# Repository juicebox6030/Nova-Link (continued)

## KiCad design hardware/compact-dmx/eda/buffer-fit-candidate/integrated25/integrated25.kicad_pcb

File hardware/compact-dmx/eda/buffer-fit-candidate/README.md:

# Buffer fit candidate — isolated proposal, 2026-10-23

**Preferred engineering candidate: Eaton HV1625-2R7256-R, 25 F**, with a local PCB aperture and lowered horizontal cradle. Conditional aged runtime is **16.343 s**, versus **9.730 s** for the existing 15 F. This is useful margin over the owner's 10 s minimum and the approximately12 s engineering screen, not measured runtime or lifetime qualification. The case remains98×34×24. No baseline or other candidate was edited. Parent must choose/integrate after Sol's concurrent startup correction.

## Sources and bounded comparison

Three families only: Eaton HV, KYOCERA AVX SCC, CDA CXHP. Actual primary PDFs and extracted text are in `sources/`; exact URLs, document identifiers and SHA256 are in `sources.json`. Eaton's primary asset was recovered through the existing browser after CLI failures. AVX and CDA were retrieved directly. Manufacturer dimension pages were rendered and inspected, with no pixel-derived dimensions.

| Exact MPN | Maximum body Ø × L mm | Initial ESR used | Aged C / ESR screen | Runtime s | Disposition |
|---|---:|---:|---:|---:|---|
| HV1325-2R7156-R |13.5×28.4|30mΩ|9.45F /60mΩ|9.730|Existing, fails conditional10s |
| **HV1625-2R7256-R** |**16.5×28.4**|27mΩ|15.75F /54mΩ|**16.343**|Preferred with explicit cutout |
| SCCT30B186SRB |13.5×32|60mΩ DC5s|11.34F /120mΩ|10.764|Little margin; body consumes3.6mm more lead reserve |
| SCCT35B226SRB |13.5×37|58mΩ DC5s|13.86F /116mΩ|13.230|Body alone exceeds35mm longitudinal reserve; not selected |
| CXHP2R7206R-TW |13.5×26.5|60mΩ DC|11.2F /120mΩ|10.631|Fits old body envelope, insufficient useful margin |

Sources: Eaton Technical Data4376 effectiveJan2020 pp2–3; AVX TDS-SC-0001 Rev11 pp2–4; CDA2024 catalog pp4,10–11. For AVX use the slower DC5s resistance, not the attractive1kHz figure. AVX maxima include +1mm diameter/+2mm length; CDA includes +1mm diameter/+1.5mm length. These are nominal starting-value substitutions only; no supplier procurement/lifecycle approval was obtained.

## Reproducible energy/ESR screen

`screen.py` independently solves constant-power discharge. With output load1.11W and electronics efficiencyη, cell terminal power is P=1.11/η. At internal voltage V and ESR R, terminal voltage is `(V+sqrt(V²−4RP))/2`; current is P/Vterminal. Stop when **loaded** terminal voltage reaches1.705917V, so internal end voltage is floor+RP/floor. Integrate `dt=C*Vterminal/P*dV` from this end to2.448V. ESR loss is explicit, not deducted twice through an assumed combined efficiency.

Initial tolerance and aging remain separate:25×0.9×0.7=15.75F. Eaton's endurance/cycle limit permits200% initial maximum ESR;54mΩ is the screen. These test limits at stated conditions are **not a field-age or cold guarantee**. Simpson integration agrees with an independent100µs forward-time integration within0.001s;10k vs20k integration panels agree within1e−8s. Existing15F result reproduces9.729548s.

At cutoff the25F screen draws0.813A and dissipates35.7mW in ESR. Manufacturer20°C references list3.4A continuous for15°C rise in open air and20A one-second pulse; neither qualifies the enclosed fixture duty cycle. At70% efficiency and twice aged ESR (108mΩ), runtime13.018s; at70% and162mΩ,11.893s. These are sensitivity allocations, **not sourced cold multipliers**. Cold capacitance can fall as well: an additional0.7 capacitance factor would reduce the latter to8.325s. Eaton does not provide a guaranteed combined aged/cold bound here. AVX typical temperature plots and CDA's temperature-change limits likewise do not establish a simultaneous lifetime/temperature guarantee for the preferred cell.

Retain2.6V nominal charging and all existing cutoff/rearm thresholds; no resistor changes proposed. Raising voltage is not the selected fix: even ignoring ESR, the aged15F needs2.5365V usable starting voltage for12s, above the existing2.448V reserved start. Removing the100mV historical reserve would require validating regulation/arming/load behavior; it is not free energy margin. At2.7V maximum rating there is no justification to consume the existing tolerance/overshoot allowance.

## Exact packaging proposal

Editable `geometry.py`, `buffer25-proposal.FCStd` and analytic `buffer25-proposal.step` are a **separate** geometry proposal. They copy frozen GCT shapes read-only; no baseline writer is imported. `fit-section.svg/pdf` are dimensioned equal-scale views.

- Existing board mainx4..94,y23..51,z10..11 and USB tongue remain. **New aperture** x26.5..55.9,y25.5..35.8,29.4×10.3 through the board; square corners are conceptual and require routed internal radius/strength/DFM design. It stays right of isolation boundaryx26 and below the RF allocationx59.
- Cell maximum body moves fromx26..54.4,cy30.25,cz18.75 to **x27..55.4,cy30.65,cz18.1**. Maximum body bottom9.85/top26.35 and y22.4..38.9. It crosses the PCB plane, so an unchanged board is impossible. High-body projection extends outside the oldy23.5..37 reserve; this is explicitly a new3D reserve, not silent reuse of its area.
- Two proposed PA12 saddles x28..31 and50..53,y25.8..35.5,z7..12.5 are cut to radius8.60. They contact the case floor atz7 and clear the aperture. Nominal radial gap0.35 is for a **not yet modeled/specified compliant liner**. Cell-position0.15 plus saddle-process0.10 leaves0.10 rigid radial margin. Positive retention, adhesive/mounting method, vent relief, load/creep and compression must be designed/qualified; no retention solution is claimed from the saddle alone.
- Supplier leads change fromØ0.60 to **Ø0.80±0.02**, pitch **7.5±0.5** (previous5mm). Existing C23 lands atx27.5 are removed from this proposal's check and must be replaced, not reused. Proposed **lead-form reservation** x55.4..58.9,y26..35.3 with potential landing nearx58 and nominaly26.9/34.4, stays before RFx59. This is an allocation only: allowable bend radius/seal standoff, lead strain relief, hole/annulus/pitch accommodation and solder volume are unresolved. No exact formed-lead CAD or released footprint is fabricated.
- GCT support/stop/port, NOR, screw bosses and external98×34×24 remain untouched. No cable-fit, PCB-strength, EMC or RF-clearance qualification follows from this geometry.

Nominal wall/lid clearance0.40/0.65mm. Inflating the maximum cell by0.15mm radially and each end gives wall0.25/lid0.50; a further0.10mm inward case/lid process allowance leaves **0.15/0.40mm**. With aperture edges inset0.10 and PCB top11.10, the inflated cell has **0.231mm** actual BRep PCB clearance. These are allocated process limits requiring manufacturer agreement, not measured assembly capability.

The independent geometry screen finds16 valid closed solids,15 cell-to-other-solid comparisons, and173 component-courtyard extrusions with **zero intersections**, plus cradle checks. Four mounting footprints have empty courtyard caches; physical bosses/holes are instead in the frozen solids. Top heights use conservative2.23mm, except nearbyU24/U26 at source DBV maximum1.45mm andR15 at deliberately loose1.45mm (Vishay actual0402 maximum0.40mm); bottom heights1.45mm. The initial uniform2.23mm screening flagged these three, then source-height refinement cleared them. This is not supplier-exact assembled component CAD. The original37 positions, USB, NOR and power placements are not edited or re-routed. **No new KiCad DRC is claimed**: this is an aperture proposal, not a modified electrical board.

## Charge, voltage, protection and release gates

25mA remains: nominal empty-to2.6V takes**43.33min before CV tail**, versus26min. Using32.5F,2.652V and22.42mA gives**64.07min before tail**, conditional on the existing charger assumptions; no recharge-interval requirement is invented. Leakage45µA is nominal after72h at20°C, not a worst-case aged/cold bound. NormalUSB still requires5V advertisement≥1.5A; no changes to qualification or current limiting.

Preferred cell rating2.7V,−40..+65°C; extension to85°C requires linear derating to2.3V.2.6V nominal is not authorized across that entire extended range.3.0V surge is not a permissible charge target. Do not reverse or overvoltage. Stored energy grows to84.5J nominal at2.6V, up to118.46J at32.5F/2.7V.100A short-circuit reference is a safety number, not operating current or protection guarantee.

Existing absence of independent cell OVP/fuse remains a **hardware protection-policy gate**: a charger feedback fault can overcharge below input-current-trip level; a cell-side short bypasses upstream protection. Larger capacitance increases fault energy. This package does not quietly add or qualify protection. Before release: supplier lead/temperature/capacitance/ESR confirmation; cell OVP/short policy; charger low-voltage behavior and leakage; empty startup/hot reattach afterU40 correction; measured worst-activity runtime at temperature/age; cradle/retainer/vent/assembly tolerance; new C23 lands and routing/PCB cutout strength; full RF/mechanical qualification.

## Concurrency and reproduction

`inputs.json` records initial read hashes; `placement-boxes.json` separately records the exact actual-board hash used for173 volume screens. Sol changed `DESIGN.md`, `corner-proof.py`, `corner-proof.json` and the live board during this pass, as expected. `screen.json` reports those changes rather than overwriting input hashes. **This proposal is against the frozen extracted geometry and fixed user-specified electrical corner, not acceptance of the final Sol revision.** Parent must compare/re-extract after integration; no power-file mutation was made here.

From repo root:

```sh
python3 hardware/compact-dmx/eda/buffer-fit-candidate/screen.py
NOVA_BUFFER_FIT="$PWD/hardware/compact-dmx/eda/buffer-fit-candidate" QT_QPA_PLATFORM=offscreen /home/juicebox/.local/bin/freecadcmd hardware/compact-dmx/eda/buffer-fit-candidate/geometry.py
python3 hardware/compact-dmx/eda/buffer-fit-candidate/draw.py
```

`extract-placement.py` is the read-only KiCad extraction tool used once; it writes only here. Do not rerun it against a changed source and call that the same evidence. `freeze.py` refuses to overwrite its initial record. `receipt.json` holds artifact/source hashes and final checks. No hardware operation, firmware, installation, publication, baseline edits or product acceptance.

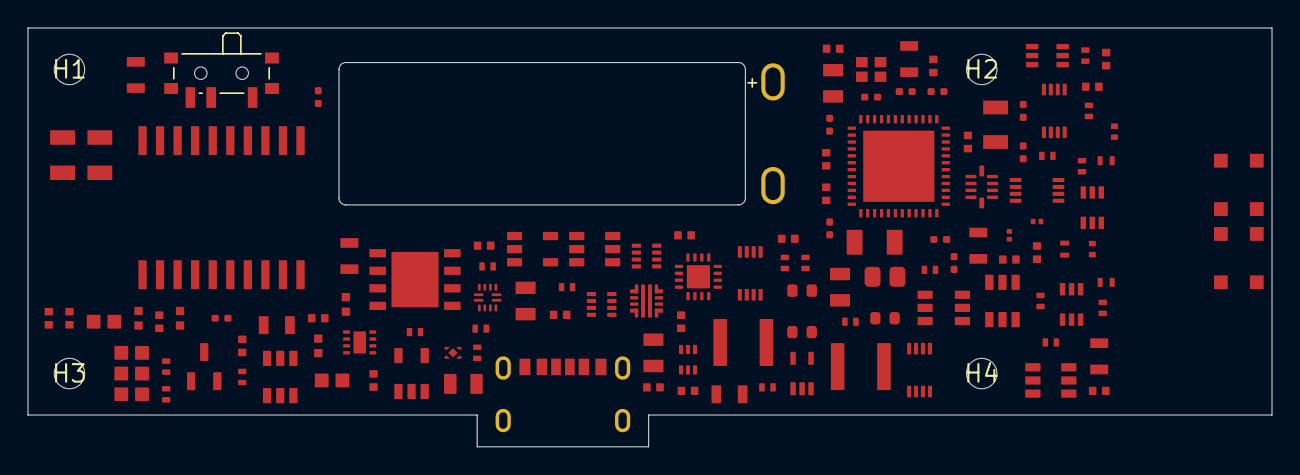
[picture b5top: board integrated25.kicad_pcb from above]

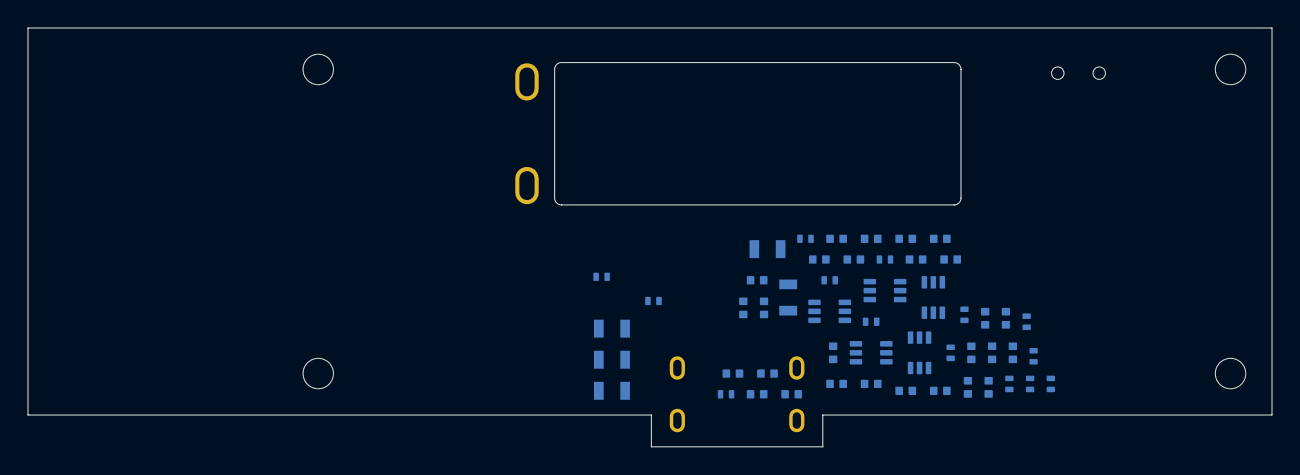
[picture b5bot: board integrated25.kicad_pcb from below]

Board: 2 copper layers, 90.0 x 30.3 mm, 178 parts (51 on the bottom side), 105 nets, no tracks yet.

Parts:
BASE_A101: 0900AD47A2450001E PROTOTYPE TUNING REQUIRED; Johanson_0900AD47_IsolatedLands
BASE_C1, BASE_C3: GRM155R71E104KE14D 100nF 25V X7R; TI_CAPC1005_Vector
BASE_C2, BASE_C4: GRM21BR71A106KE51L 10uF 10V X7R; Murata_GRM21_Reflow
BASE_C101, BASE_C102: GRM188R60J226MEA0D 22uF; TI_CAPC1608_Vector
BASE_C103: GRM155R61C105KA12D 1uF; TI_CAPC1005_Vector
BASE_C104, BASE_C105, BASE_C106, BASE_C107, BASE_C108, BASE_C109: GRM155R71E104KE14D 100nF; TI_CAPC1005_Vector
BASE_C110, BASE_C111: GRM1555C1H120JA01D 12pF; TI_CAPC1005_Vector
BASE_C112, BASE_C113: GRM0335C1H101GA01D 100pF; TI_CAPC0603_Vector
BASE_C115: GJM1555C1H1R0BB01D 1.0pF TUNE; Murata_GJM155_Manufacturer
BASE_C116: GJM1555C1H8R2DB01D 8.2pF TUNE; Murata_GJM155_Manufacturer
BASE_FL101: BLM18HE152SN1D; TI_BLM18_Vector
BASE_L101: MLZ2012N6R8LT000 6.8uH; TI_MLZ2012_Vector
BASE_L102: 0402HP-2N7XGRW 2.7nH TUNE; Coilcraft_0402HP_Manufacturer
BASE_L103: 0402HP-5N1XGRW 5.1nH TUNE; Coilcraft_0402HP_Manufacturer
BASE_L104: 0402HP-12NXGRW 12nH TUNE; Coilcraft_0402HP_Manufacturer
BASE_R1, BASE_R2, BASE_R3: CRCW040210K0FKED 10k 1%; Vishay_CRCW0402
BASE_R4: CRCW04021K00FKED 1k 1%; Vishay_CRCW0402
BASE_R_TERM1, BASE_R_TERM2: CRCW1206240RFKEA 240R 1% 0.25W; Vishay_CRCW1206
BASE_S_TERM: PCM12SMTR OFF=1-2 / ON=2-3; PCM12_PENDING_MANUFACTURER_LAND_RECHECK
BASE_TR101: 0900PC15A0036001E; TI_IPC1352_Vector
BASE_U1: CC1352R1F3RGZR; TI_RGZ0048A
BASE_U5: ISOW1412DFMR; TI_DFM0020A
BASE_Y101: FC-135 32.7680KA-AG0; Epson_FC135_Manufacturer
BASE_Y102: NX2016SA 48MHz EXS00A-CS05517; NDK_NX2016SA_Manufacturer
C1, C7, C15, C16, C17, C18, C21: GRM155R61C105KA12D 1uF 16V X5R; C0402
C2, C3, C22: GRM155R71H103KA88D 10nF 50V X7R; C0402
C4, C5, C24, C25, C26, C27, C28, C29, C30, C31, C32, C33, C34, C35, C36, C37, C38, C39, C40, C41, C42, C43, C44, C45: GRM155R71E104KE14D 100nF 25V X7R; C0402
C6, C8, C9, C10, C11, C12, C13, C14, C19, C20: GRM21BR71A106KE51L 10uF 10V X7R; C0805
C23: HV1625-2R7256-R 25F 2.7V; HV1625_formed_ENGINEERING
H1, H2, H3, H4: Mechanical NPTH 2.2
J1: USB4125-GF-A; USB_GCT
J4: Fabricated six-pad cJTAG/reset/ROM; VREF sense on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; Factory6
L1: XGL4020-222MEC 2.2uH 20%; L4020
L2: XFL4020-222MEC 2.2uH 20%; L4020
R1: TNPW1206150RBEEA 150ohm 0.1% 25ppm; R1206
R2: TNPW0805330RBEEA 330ohm 0.1% 25ppm; R0805
R3: TNPW040222K1BEED 22100ohm 0.1% 25ppm; R0402
R4, R6, R7, R8, R12, R13, R15, R21, R25, R27, R29, R31, R33, R35, R37, R38, R39, R40, R43, R44, R45, R46: TNPW040210K0BEED 10000ohm 0.1% 25ppm; R0402
R5: TNPW0805909KBEEA 909000ohm 0.1% 25ppm; R0805
R9: TNPW0805249KBEEA 249000ohm 0.1% 25ppm; R0805
R10: TNPW0805115KBEEA 115000ohm 0.1% 25ppm; R0805
R11: TNPW04023K32BEED 3320ohm 0.1% 25ppm; R0402
R14, R18: TNPW0402100RBEED 100ohm 0.1% 25ppm; R0402
R16, R17, R23, R41, R42, R47, R48, R56: TNPW0402100KBEED 100000ohm 0.1% 25ppm; R0402
R19: TNPW040211K9BEED 11900ohm 0.1% 25ppm; R0402
R20: TNPW040222K5BEED 22500ohm 0.1% 25ppm; R0402
R22: TNPW0805562KBEEA 562000ohm 0.1% 25ppm; R0805
R24: TNPW040232K4BEED 32400ohm 0.1% 25ppm; R0402
R26: TNPW040252K3BEED 52300ohm 0.1% 25ppm; R0402
R28, R32: TNPW040289K8BEED 89800ohm 0.1% 25ppm; R0402
R30, R34: TNPW040280K6BEED 80600ohm 0.1% 25ppm; R0402
R36: TNPW04024K70BEED 4700ohm 0.1% 25ppm; R0402
R49: TNPW040233K0BEED 33000ohm 0.1% 25ppm; R0402
R50, R51, R52, R53, R54, R55: TNPW040247K0BEED 47000ohm 0.1% 25ppm; R0402
S1: PCB normally-open SERVICE contact; Contact2
S2: PCB normally-open RESET contact; Contact2
U2: AT25SF161B-MHB-T; NOR8
U3: BQ25173DSGR; DSG8
U4: TPS62132RGTR; RGT16
U5: TPS61023DRLR; DRL6
U6: TPS259474LRPWR; RPW10
U7: TPS7A0225PDBVR; DBV5
U8, U10, U20: TPS3700DDCR; DDC6
U9: TPS3839G25DBZR; DBZ3
U16: TPS3831K33DQNR; DQN4
U17, U18: SN74LVC2G08DCUR; DCU8
U19, U40: TPS2116DRLR; DRL8
U24: TPS70933DBVR; DBV5
U25: TUSB320LAIRWBR; RWB12
U26: TPS3808G33DBVR; DBV6
U27: TPS3808G01DBVR; DBV6
U28: SN74LVC1G14DCKR; DCK5
U30, U32: SN74LVC1G11DCKR; DCK6
U31: SN74LVC1G0832DCKR; DCK6
U33, U34: SN74LVC2G132DCUR; DCU8
U35: SN74LVC1G3208DCKR; DCK6
U36, U37: SN74LVC2G17DCKR; DCK6
U38, U39: SN74LVC2G14DCKR; DCK6

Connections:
ANT_2G4: BASE_A101.1, BASE_C115.1, BASE_L102.2
ANT_915: BASE_A101.4, BASE_L104.2
AON_2V5: C17.1, C18.1, C24.1, C27.1, C28.1, C29.1, C30.1, C34.1, C35.1, C36.1, C37.1, C38.1, C39.1, C40.1, C41.1, C42.1, C43.1, R49.1, R50.1, R51.1, R52.1, R53.1, R56.1, U7.5, U8.5, U9.3, U10.5, U19.5, U20.5, U27.6, U30.5, U31.5, U32.5, U33.8, U34.8, U35.5, U36.5, U37.5, U38.5, U39.5
AON_OK: U9.2, U30.6, U32.3
AON_PRIORITY: R3.2, R4.1, U40.4
AON_RAW: C15.1, C16.1, U7.1, U7.3, U40.2, U40.7
AON_USB_LIMITED: C1.1, R2.2, R3.1, U40.3, U40.5
BACKUP_RAW: C8.1, C9.1, R30.1, U4.10, U4.11, U4.12, U19.2, U19.7
BOOST_3V9: C12.1, C13.1, R17.1, R22.1, R34.1, U5.6, U19.6, U40.6
BOOST_FB: R22.2, R23.1, U5.1
BOOST_NOT_READY_OD: R53.2, U20.6, U39.1
BOOST_READY: U31.3, U39.6
BOOST_SENSE: R34.2, R35.1, U20.4
BOOST_SW: L1.1, U5.5
BUCK_EN: R54.1, U4.13, U17.1, U35.4
BUCK_PG: BASE_U1.21, R36.2, U4.4, U33.6, U37.1
BUCK_PG_BUF: U27.3, U37.6
BUCK_SS: C22.1, U4.9
BUCK_SW: L2.1, U4.1, U4.2, U4.3
CAP_ARM: U34.6, U34.7, U35.3, U37.3
CAP_BAR: U34.2, U34.3
CAP_BOOST_EN: R55.1, U5.2, U37.4
CAP_OK: U32.1, U36.4
CAP_OK_OD: R50.2, U8.1, U36.3
CAP_POS: C14.1, C23.1, L1.2, R20.1, R24.1, R26.1, U3.8, U5.3
CAP_RESET_N: U32.4, U34.5
CAP_SAFE_PATH: U31.4, U32.6
CAP_SENSE: R24.2, R25.1, U8.3
CAP_SET_N: U33.7, U34.1
CAP_START_N_OD: R51.2, U8.6, U38.1
CAP_START_OK: U33.2, U38.6
CAP_START_SENSE: R26.2, R27.1, U8.4
CC1: J1.A5, U25.1
CC2: J1.B5, U25.2
CC_3V3: C20.1, C25.1, C26.1, C33.1, R6.1, R7.1, R8.1, R10.1, U24.5, U25.12, U26.5, U26.6, U28.5
CC_ADVERT_OK: U26.3, U28.4
CC_ALLOW: R9.1, R10.2, U6.1, U26.1, U30.3
CC_OUT1: R6.2, U25.7, U28.2
CC_OUT2: R7.2, U25.8
CC_RAW: C19.1, R1.2, U24.1, U24.3
CC_VBUS_DET: R5.2, U25.4
CHARGE_DISABLE: R56.2, U3.3, U33.3
DCDC_SW: BASE_L101.1, BASE_U1.33
DCOUPL: BASE_C103.1, BASE_U1.23
DMX_DE_SAFE: BASE_R1.1, BASE_U5.3, U17.3
DMX_N: BASE_R_TERM1.2, BASE_R_TERM2.2, BASE_U5.18, BASE_U5.19
DMX_P: BASE_S_TERM.2, BASE_U5.17, BASE_U5.20
DMX_POWER_EN: BASE_R3.1, BASE_R4.1, U18.7
EFUSE_DVDT: R14.1, U6.7
EFUSE_DVDT_C: C2.1, R14.2
EFUSE_ILM: R11.1, U6.9
EFUSE_PGTH: R12.2, R13.1, U6.4
EFUSE_TIMER: C3.1, U6.10
FLASH_HOLD_N: R46.2, U2.7
FLASH_WP_N: R45.2, U2.3
GND_ISO: BASE_C3.2, BASE_C4.2, BASE_U5.11, BASE_U5.13, BASE_U5.14, BASE_U5.15
GND_USB: BASE_C1.2, BASE_C2.2, BASE_C101.2, BASE_C102.2, BASE_C103.2, BASE_C104.2, BASE_C105.2, BASE_C106.2, BASE_C107.2, BASE_C108.2, BASE_C109.2, BASE_C110.2, BASE_C111.2, BASE_C113.2, BASE_C115.2, BASE_C116.2, BASE_L103.2, BASE_R1.2, BASE_R3.2, BASE_TR101.2, BASE_TR101.3, BASE_TR101.10, BASE_U1.49, BASE_U5.6, BASE_U5.10, BASE_Y102.2, BASE_Y102.4, C1.2, C2.2, C3.2, C4.2, C5.2, C6.2, C7.2, C8.2, C9.2, C10.2, C11.2, C12.2, C13.2, C14.2, C15.2, C16.2, C17.2, C18.2, C19.2, C20.2, C21.2, C22.2, C23.2, C24.2, C25.2, C26.2, C27.2, C28.2, C29.2, C30.2, C31.2, C32.2, C33.2, C34.2, C35.2, C36.2, C37.2, C38.2, C39.2, C40.2, C41.2, C42.2, C43.2, C44.2, C45.2, J1.A12, J1.B12, J1.SH, J4.2, R4.2, R8.2, R9.2, R11.2, R13.2, R15.2, R16.2, R17.2, R19.2, R21.2, R23.2, R25.2, R27.2, R29.2, R31.2, R33.2, R35.2, R41.2, R42.2, R47.2, R48.2, R54.2, R55.2, S1.2, S2.2, U2.4, U2.9, U3.4, U3.9, U4.5, U4.6, U4.7, U4.8, U4.15, U4.16, U4.17, U5.4, U6.2, U6.8, U7.2, U8.2, U9.1, U10.2, U16.3, U16.5, U17.4, U18.4, U18.5, U18.6, U19.1, U20.2, U24.2, U25.3, U25.10, U25.11, U26.2, U27.2, U28.3, U30.2, U31.2, U32.2, U33.4, U34.4, U35.2, U36.2, U37.2, U38.2, U39.2, U39.3, U40.1
ICHG_FILTER: C4.1, R18.2, R19.1
ICHG_PIN: R18.1, U3.2
ISOW_EN_PIN: BASE_R4.2, BASE_U5.8
ISO_3V3: BASE_C3.1, BASE_C4.1, BASE_U5.12, BASE_U5.16
LIMITED_5V: C6.1, C7.1, R12.1, R16.1, R28.1, U3.1, U6.6, U19.3
MAIN_NOT_READY_OD: R52.2, U10.6, U38.3
MAIN_READY: U31.1, U35.6, U38.4
MAIN_SENSE: R30.2, R31.1, U10.4
MANUAL_RESET_N: J4.5, R38.2, S2.1, U16.2
MCU_DE_REQUEST: BASE_U1.10, R41.1, U17.5
MCU_DMX_RX: BASE_U1.18, BASE_U5.4
MCU_DMX_TX: BASE_U1.19, BASE_U5.2
MCU_ISO_REQUEST: BASE_U1.11, R42.1, U18.1
MCU_RE_N: BASE_R2.2, BASE_U1.12, BASE_U5.5, R43.2
MCU_VDDR: BASE_C102.1, BASE_C108.1, BASE_C109.1, BASE_L101.2, BASE_U1.45, BASE_U1.48
MCU_VDDS: BASE_C101.1, BASE_C104.1, BASE_C105.1, BASE_C106.1, BASE_C107.1, BASE_FL101.1, BASE_U1.13, BASE_U1.22, BASE_U1.34, BASE_U1.44
RAW_SENSE: R32.2, R33.1, U20.3
RESET_OK: BASE_U1.35, U16.1, U17.2
RF_2G4_50: BASE_L102.1, BASE_TR101.1
RF_915_50: BASE_C112.2, BASE_C116.1, BASE_L103.1, BASE_L104.1
RF_915_UNBLOCKED: BASE_C112.1, BASE_TR101.4
RF_N_2_4GHZ: BASE_TR101.8, BASE_U1.2
RF_N_SUB_1GHZ: BASE_TR101.6, BASE_U1.4
RF_P_2_4GHZ: BASE_TR101.9, BASE_U1.1
RF_P_SUB_1GHZ: BASE_TR101.7, BASE_U1.3
ROM_BOOT_STRAP: BASE_U1.8, J4.6, R40.2
RX_TX: BASE_C113.1, BASE_TR101.5, BASE_U1.5
SERVICE_N_DISTINCT_GPIO: BASE_U1.9, R39.2, S1.1
SOURCE_SENSE: U30.1, U36.6
SOURCE_SENSE_OD: R49.2, U6.3, U10.1, U20.1, U36.1
SOURCE_VALID: U19.4, U27.5, U30.4, U31.6, U33.1, U33.5, U35.1
SPI_CS_N: BASE_U1.17, R44.2, U2.1
SPI_MISO: BASE_U1.14, U2.2
SPI_MOSI: BASE_U1.15, R48.1, U2.5
SPI_SCK: BASE_U1.16, R47.1, U2.6
SYS_3V3: BASE_C1.1, BASE_C2.1, BASE_FL101.2, BASE_R2.1, BASE_U5.1, BASE_U5.9, C10.1, C11.1, C21.1, C31.1, C32.1, C44.1, C45.1, J4.1, L2.2, R36.1, R37.1, R38.1, R39.1, R40.1, R43.1, R44.1, R45.1, R46.1, U2.8, U4.14, U16.4, U17.8, U18.8
SYS_READY: U17.6, U17.7, U18.2
TCKC: BASE_U1.25, J4.4
TERM_SW: BASE_R_TERM1.1, BASE_R_TERM2.1, BASE_S_TERM.3
TMSC: BASE_U1.24, J4.3
USB_SENSE: R28.2, R29.1, U10.3
VBUS_GOOD_3V3: BASE_U1.20, R37.2, U27.1
VBUS_RAW: C5.1, J1.A9, J1.B9, R1.1, R2.1, R5.1, R15.1, R32.1, U6.5
VCHG_FB: R20.2, R21.1, U3.7
X32K_Q1: BASE_C110.1, BASE_U1.6, BASE_Y101.1
X32K_Q2: BASE_C111.1, BASE_U1.7, BASE_Y101.2
X48M_N: BASE_U1.46, BASE_Y102.3
X48M_P: BASE_U1.47, BASE_Y102.1

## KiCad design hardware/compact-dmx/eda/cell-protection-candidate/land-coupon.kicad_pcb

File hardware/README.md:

# NOVA-LINK hardware development checkpoint

This folder preserves the TI-only dual-band DMX/RDM sidecar and rotating USB-C
power-barrel design work. **Prototype development only; not released for
manufacture.** The 2026-10-25 owner request authorizes committing and pushing this
checkpoint to `main`; it does not change the engineering acceptance status.

- [Canonical requirements, decisions and remaining gates](../docs/hardware/DMX_Dongle_and_Power_Barrel.md)
- [CAD/EDA package index and revision comparisons](compact-dmx/README.md)
- [Latest closure-access CAD, STEP and drawing](compact-dmx/rotary-compact-candidate/closure-access-margin-fix/README.md)
- [25 F sidecar placement and protection candidate](compact-dmx/eda/buffer-fit-candidate/protected25-placement/README.md)
- [Bounded power-source comparison](compact-dmx/rotary-compact-candidate/compact-source-reference-screen/README.md)
- [Fixture reference manifest](../docs/hardware/fixture-reference-manifest.md)
- [Candidate BOM](../docs/hardware/dmx-hardware-bom.csv)

Earlier candidates include failed and superseded designs, retained for comparison.
Passing ERC, geometric checks or calculations does not establish full PCB routing,
RF performance, runtime, fixture fit, mains safety, thermal performance or durable
motion. Use the canonical checkpoint to distinguish current development directions
from historical allocations and unresolved construction.

Editable project files, our generated CAD/STEP/drawings, scripts, original analysis
and source/validation manifests are versioned. Downloaded manufacturer PDFs, CAD,
reference archives, full-page vendor previews, tool caches and automatic backups
remain local and ignored. Exact original URLs and hashes are retained in the
source manifests; third-party redistribution rights are not asserted. A fresh
clone therefore needs the referenced source files before source-dependent checks
can run. Historic absolute workspace paths and frozen-input hashes are provenance
records, not promises of a turnkey build on a new host. Follow the local
reproduction instructions for each candidate; preserve original receipts when
regenerating artifacts.

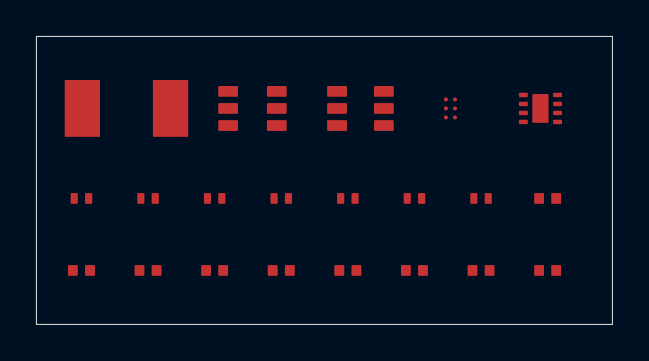
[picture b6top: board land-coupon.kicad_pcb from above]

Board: 2 copper layers, 32.0 x 16.0 mm, 21 parts (0 on the bottom side), 11 nets, no tracks yet.

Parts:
C101, C102, C203: GRM155R71E104KE14D 100nF; C0402
C103, C104, C201, C202: GRM155R61C105KA12D 1uF; C0402
F101: 045101.5MRL 1.5A non-resettable; Fuse451
R101: TNPW040256K5BYED 56500ohm; R0402
R102, R104, R202: TNPW040210K0BYED 10000ohm; R0402
R103: TNPW040282K0BYED 82000ohm; R0402
R105: TNPW040256K0BYED 56000ohm; R0402
R201: TNPW040222K2BYED 22200ohm; R0402
R203: TNPW040211K9BEED 11900ohm; R0402
R204: TNPW0402100RBEED 100ohm; R0402
U101: TPS3700DDCR; DDC6
U102: TPS3808G33DBVR; DBV6
U103: TPS22963CYZPR; YZP6
U104: BQ25173DSGR; DSG8

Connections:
CAP_POS: C202.1, F101.2, R201.1, U104.8
CELL_OV_SENSE: R101.2, R102.1, U101.4
CELL_TAB_POS: F101.1, R101.1
CHARGER_IN_PROTECTED: C104.1, C201.1, U103.A1, U103.B1, U104.1
CHARGER_PERMIT_OD: R103.2, R104.1, U101.6, U102.1
CHARGER_SWITCH_ON: R104.2, R105.1, U103.C2
GND_USB: C101.2, C102.2, C103.2, C104.2, C201.2, C202.2, C203.2, R102.2, R105.2, R202.2, R203.2, U101.2, U101.3, U102.2, U103.C1, U104.4, U104.9
ICHG_FILTER: C203.1, R203.1, R204.2
ICHG_PIN: R204.1, U104.2
LIMITED_5V: C101.1, C102.1, C103.1, R103.1, U101.5, U102.3, U102.5, U102.6, U103.A2, U103.B2
VCHG_FB: R201.2, R202.1, U104.7

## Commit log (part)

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2025-05-15 new file: .gitignore new file: LICENSE new file: README.md config/ docs/ include/ platform/ plugins/ src/ tools/
2025-05-16 new file: config/.keep new file: docs/.keep new file: include/.keep new file: platform/.keep new file: plugins/.keep new file: src/.keep new file: tools/.keep
2025-05-16 modified: README.md
2025-05-16 modified: README.md
    modified: README.md
2025-05-16 new file: docs/Architecture.md new file: docs/DataFragment_Format.md new file: docs/Development_Roadmap.md new file: docs/OSI_Model.md new file: docs/Plugin_API.md new file: docs/Zone_Management.md
2025-05-16 modified: docs/Development_Roadmap.md
2025-05-20 modified: docs/Architecture.md new file: docs/Background.adoc deleted: docs/DataFragment_Format.md deleted: docs/Plugin_API.md new file: docs/api_development.adoc new file: docs/host_firmware.adoc ne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
